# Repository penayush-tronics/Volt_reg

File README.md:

# Simple Voltage Regulator Board

This is a simple voltage regulator board, which takes in between 6.5V and upto 20V input, and outputs both 5V and 3.3V, with a maximum current output of 1A. This project uses the well-known AMS1117 step-down linear voltage regulators, which are Low Dropout Regulators, meaning the voltage drop across them is less than normal linear regulators. Here there are 2 of them, 1 of which steps down (decreases) 6.5V-20V to 5V, and the other one which steps down 5V from the previous LDO, into 3.3V. 

# How to use the board: 

Here is a 3D model of the board: 

You will see 3 screw terminal blocks; 1 on the top side, and 2 on the bottom. The one on top, labelled IN is the input block. Here, you should screw in the input wires, which can be from a battery or any power source up to 20V. Be mindful of the polarity! You can see GND is labelled next to the ground input. 

Next, to turn the board on, add a short jumper to the 3 header pins next to the input. Short/connect the top 2 pins to connect the board to power. To disconnect, move the jumper to the bottom 2 pins. After turning it on, you will see the red LED glow. This means the 5V output and the board is turned on. You can now connect the 5V output (on the bottom left side) to anything you want to power, but once again be mindful of polarity. It is labelled on the board. 

To turn on the 3.3V output, use a short header to connect the 2 header pins in the center of the board. Now the 3.3V output is turned on (bottom right side of board) and you can connect it to anything that runs on 3.3V, such as microcontrollers and development boards. 

# Why I made this board

I found myself struggling to power my electronic components, such as motors with an arduino. You cannot run them directly with the 5V output of the arduino due to current constraints, as well as you risk frying the arduino. In such cases I struggled to power them seperately with a quality, high current power source. Normal batteries and Li-Ion rechargable batteries do not have the required voltage either, and running from USB power is not ideal. Hence I developed this regulator board, so a stable and proper 5V and 3.3V power source can be used for projects.

# Schematics 

# PCB design 

KiCAD editor:

3D model-

Front side: 

Back side:

All Schematics and PCB file (including gerber zip) is available in the PCB files directory.

# It works! (Demo)

  After gathering all the parts and the PCB, I hand soldered the board together and it all works!

  I have covered the red LED because it was blindingly bright!

  Powering it using 2 Li-Ion batteries, total voltage of ~7.5V-8V

  Here is a video showing the voltage in and out using a multimeter. 

  https://github.com/user-attachments/assets/61b3c373-3d1c-4dd0-ad89-5317c5041c4e

# Bill of materials

| Item | Qty. | Price (INR) | Ext. (INR) | Link |
| :--- | :--- | :--- | :--- | :--- |
| AMS1117-3.3V, 1A, SOT-223 Voltage Regulator IC | 2 | 9.00 | 18.00 | [Link](https://robu.in/product/ams1117-3-3v-1a-sot-223-voltage-regulator-ic-pack-of-5-ics/) |
| AMS1117-5.0V, 1A, SOT-223 Voltage Regulator IC | 2 | 6.00 | 12.00 | [Link](https://robu.in/product/ams1117-5-0v-1a-sot-223-voltage-regulator-ic-pack-of-5-ics/) |
| 100uF 25V Electrolytic Capacitor | 3 | 4.18 | 12.54 | [Link](https://robu.in/product/100uf-25v-electrolytic-capacitor-pack-of-10/) |
| 3mm Red DIP LED | 16 | 0.63 | 10.08 | [Link](https://robu.in/product/3mm-red-dip-led-pack-of-50/) |
| HY1H100M050110CD288-HYNCDZ-10uF 50V Aluminum Electrolytic | 16 | 0.65 | 10.40 | [Link](https://robu.in/product/hy1h100m050110cd288-hyncdz-10uf-50v-1-82%cf%89100khz-%c2%b120-120ma100khz-plugind5xl11mm-aluminum-electrolytic-capacitors-leaded-rohs/) |
| ERS1HM220D12OT-AISHI -22uF 50V Aluminum Electrolytic | 5 | 2.00 | 10.00 | [Link](https://robu.in/product/ers1hm220d12ot-aishi-22uf-50v-%c2%b120-plugind5xl12mm-aluminum-electrolytic-capacitors-leaded-rohs/) |
| 2 Pin 5.08mm Pitch Plug-in Screw Terminal Block | 3 | 7.00 | 21.00 | [Link](https://robu.in/product/kf301-2-pin-5-08mm-pitch-plug-in-screw-terminal-block-connector-pack-of-5/) |
| 100nf 50v Disc Capacitor | 10 | 1.00 | 10.00 | [Link](https://robu.in/product/100nf-50v-disc-capacitor/) |
| 1k Ohm 0.25W Metal Film Resistor | 35 | 0.29 | 10.15 | [Link](https://robu.in/product/1k-ohm-0-25w-metal-film-resistor-pack-of-100/) |
| PCB Fabrication | 5 | 159.8 | 943 (799 + 18% tax) | [Link](lioncircuits.com) |

Total: 1057.17 INR  (114.17 INR for components)
       
       $11.51 USD ($1.24 USD for components)

       Per board cost ~220 rs ($2.40)

Also in .csv format, in BOM.csv

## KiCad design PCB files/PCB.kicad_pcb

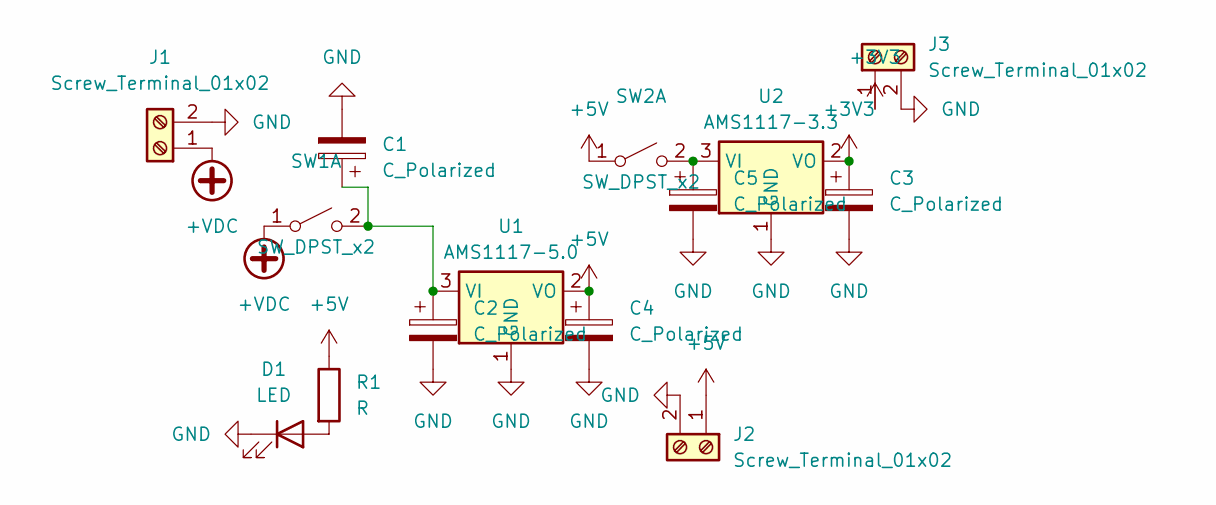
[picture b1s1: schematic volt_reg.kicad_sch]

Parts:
C1: C_Polarized; CP_Radial_D5.0mm_P2.50mm
C2, C3, C4, C5: C_Polarized; CP_Radial_D4.0mm_P1.50mm
D1: LED; LED_D3.0mm
J1, J2, J3: Screw_Terminal_01x02; TerminalBlock_MaiXu_MX126-5.0-02P_1x02_P5.00mm
R1: R; R_Axial_DIN0204_L3.6mm_D1.6mm_P5.08mm_Horizontal
SW1: SW_DPST_x2; PinHeader_1x03_P2.54mm_Vertical
SW2: SW_DPST_x2; PinHeader_1x02_P2.54mm_Vertical
U1: AMS1117-5.0; SOT-223-3_TabPin2
U2: AMS1117-3.3; SOT-223-3_TabPin2

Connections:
+3V3: C3.1, J3.1, U2.2 (VO)
+5V: C4.1, J2.1, R1.1, SW2.1 (A), U1.2 (VO)
+VDC: J1.1, SW1.1 (A)
GND: C1.2, C2.2, C3.2, C4.2, C5.2, D1.1 (K), J1.2, J2.2, J3.2, U1.1 (GND), U2.1 (GND)
unnamed: D1.2 (A), R1.2
unnamed: C1.1, C2.1, SW1.2 (B), U1.3 (VI)
unnamed: C5.1, SW2.2 (B), U2.3 (VI)

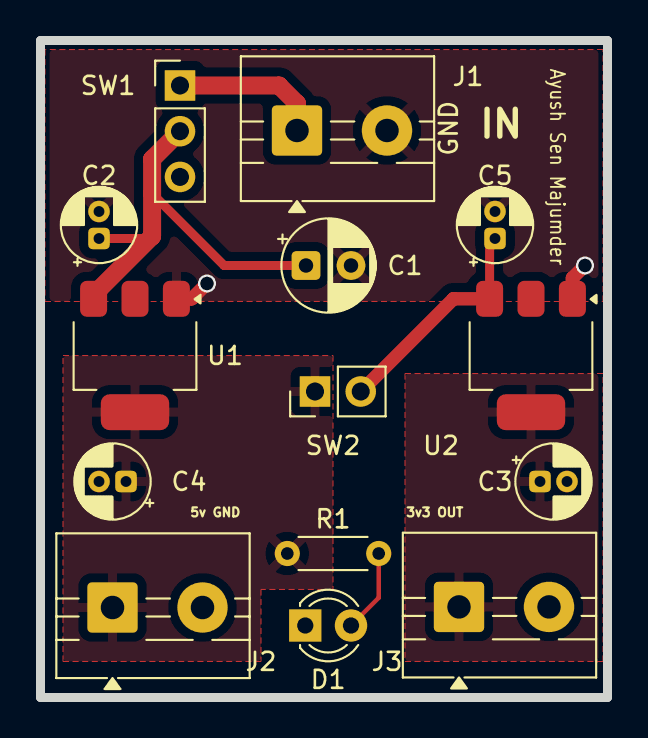
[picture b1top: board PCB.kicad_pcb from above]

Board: 2 copper layers, 31.5 x 36.5 mm, 14 parts (0 on the bottom side), 7 nets.

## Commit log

2026-03-10 Updated the repo for complete project
2026-03-10 Better screenshots
2026-03-10 Updated BOM
2026-03-10 Added PCB KiCAD
2026-03-10 Made the README better
2026-03-11 updated BOM in readme and .csv
2026-03-13 fixed per board cost
2026-05-23 Added demo section to README and required media.
2026-05-23 updated video
2026-05-23 tryign to make video work
2026-05-23 trying to make video work again.
2026-05-23 video work
